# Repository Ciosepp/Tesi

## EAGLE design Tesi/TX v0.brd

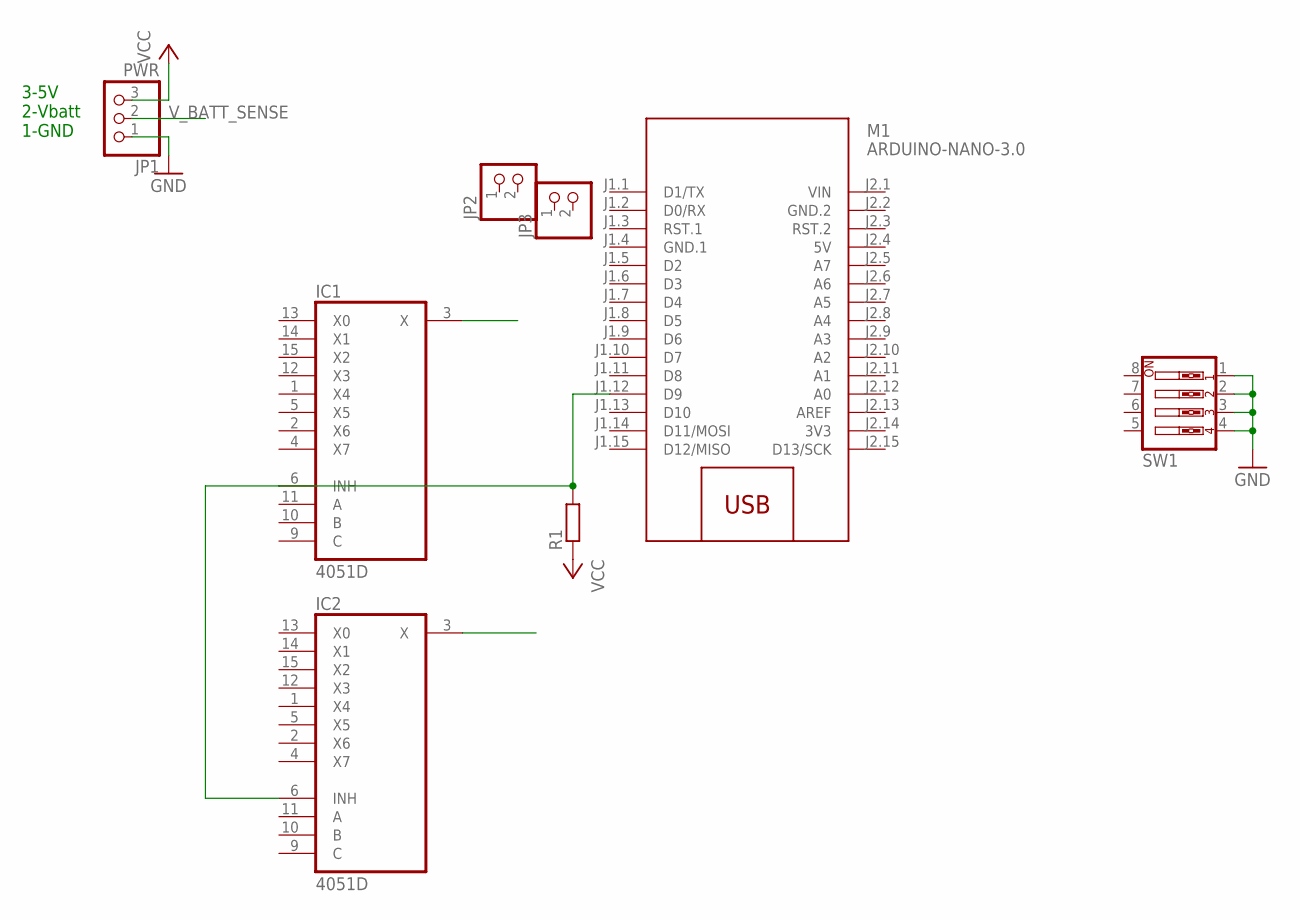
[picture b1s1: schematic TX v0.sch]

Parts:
IC1, IC2: 4051D; SO16
JP1: PWR; 1X03
JP2, JP3: PINHD-1X2; 1X02
M1: ARDUINO-NANO-3.0
R1: R-EU_0411/15; 0411/15
SW1: SW_DIP-4; EDG-04

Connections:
3V3: M1.J2.14 (3V3)
5V: M1.J2.4 (5V)
GND: IC1.8 (GND), IC2.8 (GND), JP1.1, SW1.1, SW1.2, SW1.3, SW1.4
GND.1: M1.J1.4 (GND.1)
GND.2: M1.J2.2 (GND.2)
unnamed: IC1.6 (INH), IC2.6 (INH), M1.J1.12 (D9), R1.2
VCC: IC1.16 (VCC), IC2.16 (VCC), JP1.3, R1.1
VEE: IC1.7 (VEE), IC2.7 (VEE)
VIN: M1.J2.1 (VIN)
V_BATT_SENSE: JP1.2

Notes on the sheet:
3-5V 2-Vbatt 1-GND

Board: 2 copper layers, 8 parts (0 on the bottom side), 4 nets, no tracks yet.

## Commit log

2023-03-03 New PCB done
2024-10-25 import
2024-10-28 added material
2024-11-05 vs imp
2024-11-06 Almost right dim
2024-11-06 traindata shape ok
2024-11-07 First succ run
2024-11-08 roc graph
2024-11-09 acq done
2024-11-10 11-11
2024-11-11 1111-a
2024-11-11 1111b

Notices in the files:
parts and their libraries:
diy-modules: Released under the Creative Commons Attribution 4.0 International License: http://creativecommons.org/licenses/by/4.0
